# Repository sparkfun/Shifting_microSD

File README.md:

SparkFun Shifting µSD
===================================
![SparkFun Shifting µSD
](https://cdn.sparkfun.com/assets/learn_tutorials/4/5/2/shifting__SD.jpg)

[*SparkFun Shifting µSD
 (DEV-13743)*](https://www.sparkfun.com/products/13743)

 Breakout board for the microSD socket that is not much bigger than your fingernail. Compatible with the SPI interface found on any SD card, this tiny form factor was created for cell phone storage and is perfect for your next data logging project!

Repository Contents
-------------------

* **/Hardware** &mdash; All Eagle design files (.brd, .sch)
* **/Firmware** &mdash; A trivial write only Arduino word processor.
* **/Production** &mdash; Test bed files and production panel files

Documentation
--------------
* **[Hookup Guide](https://learn.sparkfun.com/tutorials/microsd-breakout-with-level-shifter-hookup-guide)** &mdash; Basic hookup guide for the Shifting µSD.
* **[SparkFun Fritzing repo](https://github.com/sparkfun/Fritzing_Parts)** &mdash; Fritzing diagrams for SparkFun products.
* **[GitHub Repository](https://github.com/sparkfun/Shifting_microSD)** &mdash; Hardware design files and source code.

Product Versions
----------------
* [DEV-13743](https://www.sparkfun.com/products/13743) &mdash; µSD socket with integrated level shifter
* [BOB-00544](https://www.sparkfun.com/products/544) &mdash; µSD socket (3.3V)

Version History
---------------
* [V_10](https://www.sparkfun.com/products/13743) &mdash; Initial release

License Information
-------------------

This product is _**open source**_!

Please review the LICENSE.md file for license information.

If you have any questions or concerns on licensing, please contact TechSupport@SparkFun.com.

Distributed as-is; no warranty is given.

&mdash; Your friends at SparkFun.

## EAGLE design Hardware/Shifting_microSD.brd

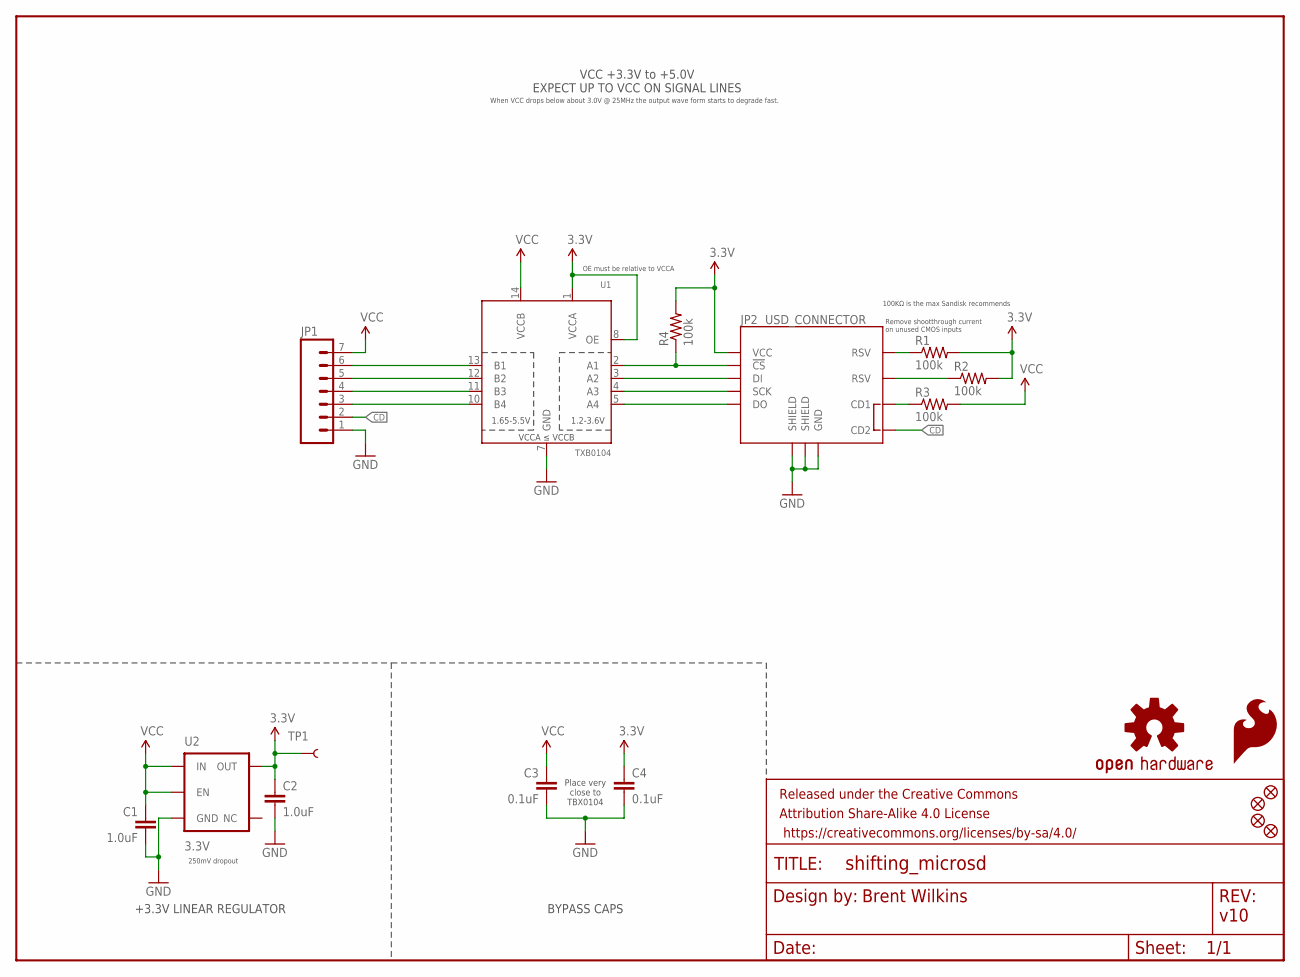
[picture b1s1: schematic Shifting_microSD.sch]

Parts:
C1, C2: 1.0uF; 0603-CAP
C3, C4: 0.1uF; 0603-CAP
FID1, FID2, FID3, FID4: FIDUCIAL1X2; FIDUCIAL-1X2
FRAME1: FRAME-LETTER; CREATIVE_COMMONS
JP1: M07; 1X07
JP2: USD_CONNECTOR; MICRO-SD-SOCKET-PP
LOGO1: SFE_LOGO_FLAME.2_INCH; SFE_LOGO_FLAME_.2
LOGO2: OSHW-LOGOS; OSHW-LOGO-S
R1, R2, R3, R4: 100k; 0603-RES
TP1: TEST-POINT3; PAD.03X.03
U1: TXB0104; SO14
U2: 3.3V; SOT23-5

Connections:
3V3: C2.1, C4.1, JP2.VCC, R1.2, R2.2, R4.2, TP1.P$1, U1.1 (VCCA), U1.8 (OE), U2.5 (OUT)
!CS_3V3: JP2.CS (!CS), R4.1, U1.2 (A1)
CD: JP1.2, JP2.CD2
CDSDSD: JP2.CD1, R3.1
DI: JP1.5, U1.12 (B2)
DI_3V3: JP2.DI, U1.3 (A2)
DO: JP1.3, U1.10 (B4)
DO_3V3: JP2.DO, U1.5 (A4)
GND: C1.2, C2.2, C3.2, C4.2, JP1.1, JP2.GND, JP2.GND1 (SHIELD), JP2.GND3 (SHIELD), U1.7 (GND), U2.2 (GND)
unnamed: JP1.6, U1.13 (B1)
unnamed: JP1.4, U1.11 (B3)
RSV@1: JP2.RSV1 (RSV), R1.1
RSV@2: JP2.RSV2 (RSV), R2.1
SCK_3V3: JP2.SCLK (SCK), U1.4 (A3)
VDD_IO: C1.1, C3.1, JP1.7, R3.2, U1.14 (VCCB), U2.1 (IN), U2.3 (EN)

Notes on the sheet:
Brent Wilkins
v10
VCC +3.3V to +5.0V EXPECT UP TO VCC ON SIGNAL LINES
Remove shootthrough current on unused CMOS inputs
Place very close to TBX0104
OE must be relative to VCCA
When VCC drops below about 3.0V @ 25MHz the output wave form starts to degrade fast.
+3.3V LINEAR REGULATOR
BYPASS CAPS
100KΩ is the max Sandisk recommends
250mV dropout

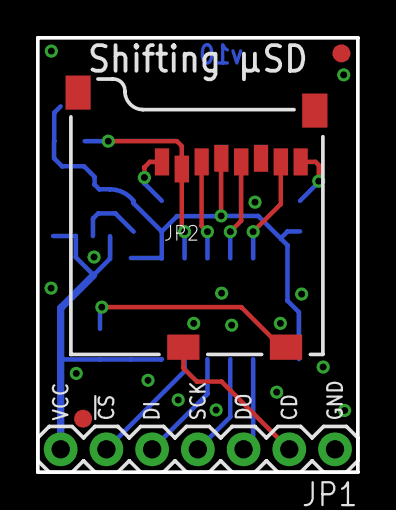
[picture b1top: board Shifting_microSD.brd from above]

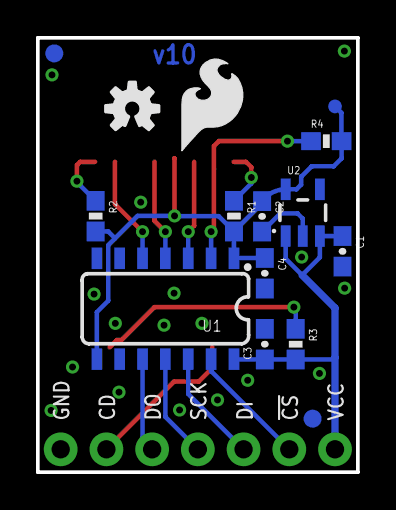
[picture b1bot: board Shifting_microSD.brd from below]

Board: 2 copper layers, 17.8 x 24.1 mm, 20 parts (15 on the bottom side), 15 nets.

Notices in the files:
parts and their libraries:
SparkFun-Connectors: Licensing: CC v3.0 Share-Alike You are welcome to use this library for commercial purposes.
SparkFun-Aesthetics: Licensing: Creative Commons ShareAlike 4.0 International - https://creativecommons.org/licenses/by-sa/4.0
SparkFun-Aesthetics: Released under the Creative Commons
